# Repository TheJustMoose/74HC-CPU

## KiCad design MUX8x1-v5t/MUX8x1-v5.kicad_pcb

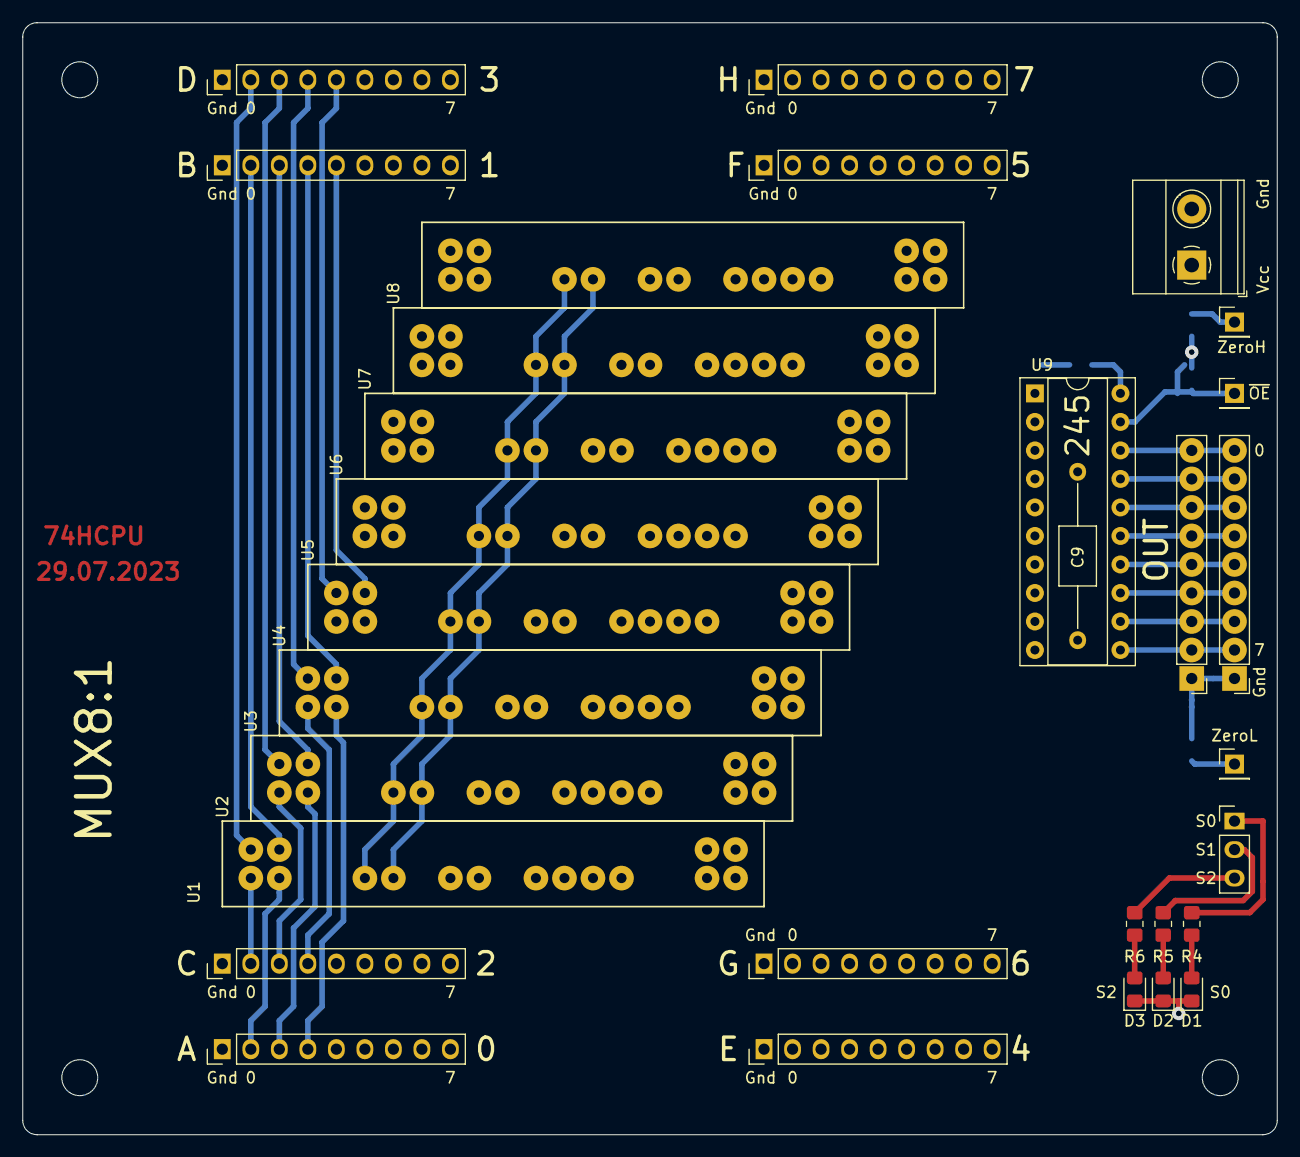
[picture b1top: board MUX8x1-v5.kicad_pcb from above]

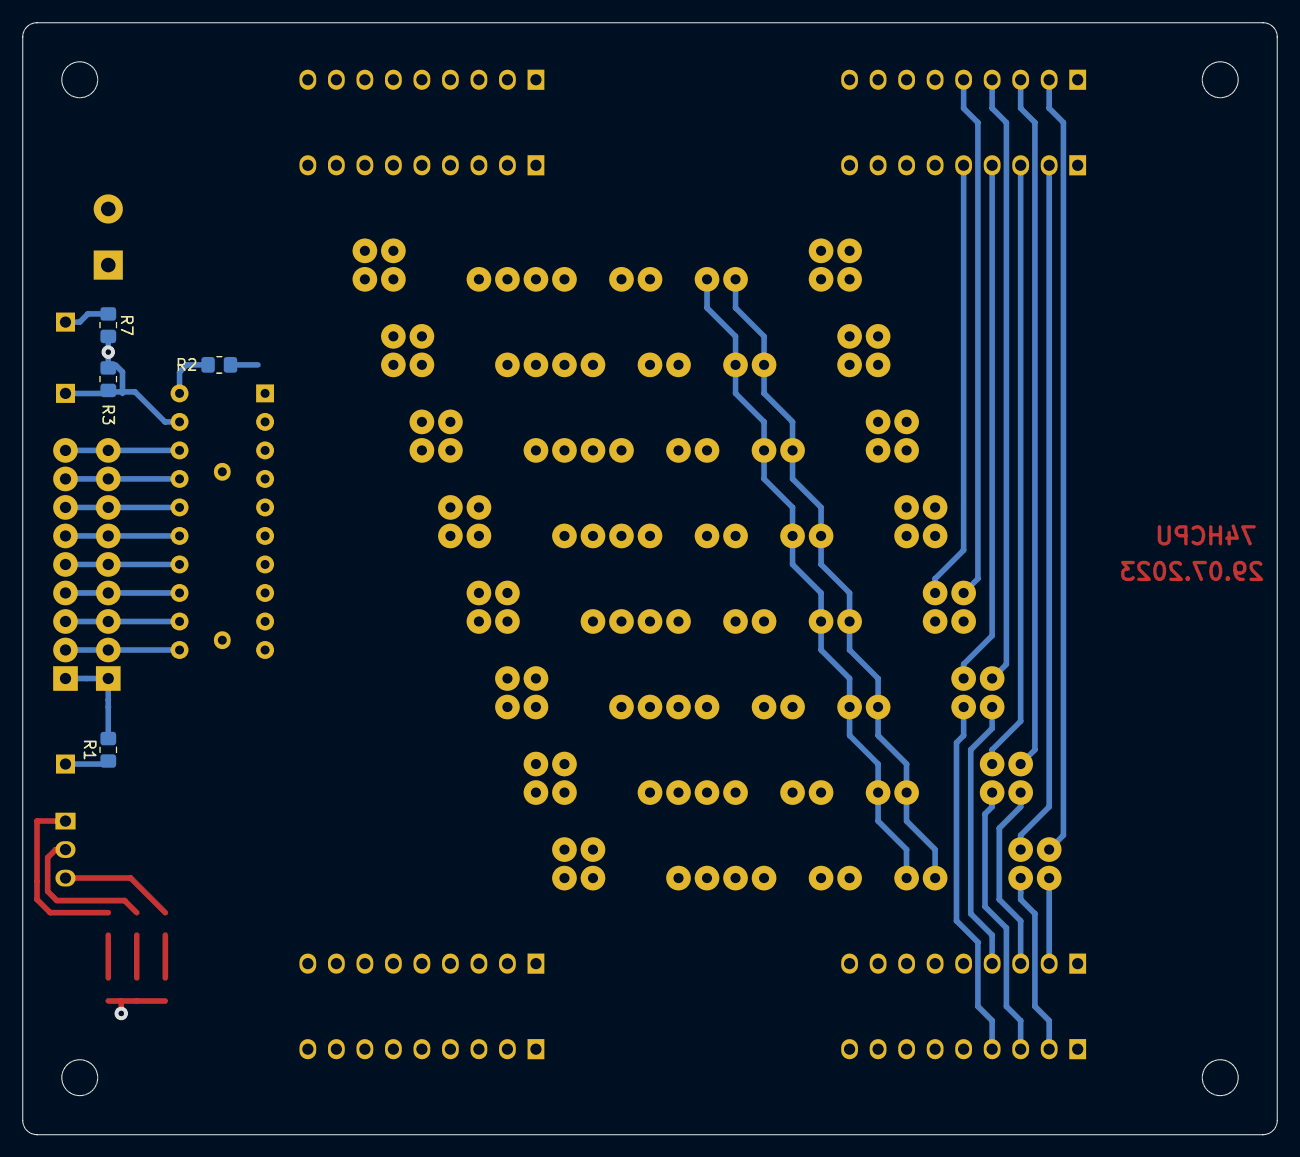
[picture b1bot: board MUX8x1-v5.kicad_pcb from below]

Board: 2 copper layers, 111.8 x 99.1 mm, 39 parts (4 on the bottom side), 92 nets.

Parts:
C9: 0.1uF; C_Axial_L5.1mm_D3.1mm_P15.00mm_Horizontal
D1, D2, D3: LED; LED_0805_2012Metric_Pad1.15x1.40mm_HandSolder
H1, H2, H3, H4: MountingHole; MountingHole_3.2mm_M3
J1, J2, J3, J5, J6, J11, J12, J15, J16, J21: Conn_01x09_Male; PinHeader_1x09_P2.54mm_Vertical
J7, J13, J20: Conn_01x01_Male; PinHeader_1x01_P2.54mm_Vertical
J9: Screw_Terminal_01x02; TerminalBlock_Phoenix_MKDS-1,5-2_1x02_P5.00mm_Horizontal
J10: Conn_01x03_Male; PinHeader_1x03_P2.54mm_Vertical
R1, R2, R3, R7: 10k; R_0805_2012Metric_Pad1.20x1.40mm_HandSolder
R4, R5, R6: 1k; R_0805_2012Metric_Pad1.20x1.40mm_HandSolder
U1, U2, U3, U4, U5, U6, U7, U8: 74LS151; MUX8-1
U9: 74HC245; DIP-20_W7.62mm_Socket

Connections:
/A0: J1.2, U1.4
/A1: J1.3, U2.4
/A2: J1.4, U3.4
/A3: J1.5, U4.4
/A4: J1.6, U5.4
/A5: J1.7, U6.4
/A6: J1.8, U7.4
/A7: J1.9, U8.4
/B0: J5.2, U1.3
/B1: J5.3, U2.3
/B2: J5.4, U3.3
/B3: J5.5, U4.3
/B4: J5.6, U5.3
/B5: J5.7, U6.3
/B6: J5.8, U7.3
/B7: J5.9, U8.3
/BUS0: J3.2, J21.2, U9.11
/BUS1: J3.3, J21.3, U9.12
/BUS2: J3.4, J21.4, U9.13
/BUS3: J3.5, J21.5, U9.14
/BUS4: J3.6, J21.6, U9.15
/BUS5: J3.7, J21.7, U9.16
/BUS6: J3.8, J21.8, U9.17
/BUS7: J3.9, J21.9, U9.18
/C0: J11.2, U1.2
/C1: J11.3, U2.2
/C2: J11.4, U3.2
/C3: J11.5, U4.2
/C4: J11.6, U5.2
/C5: J11.7, U6.2
/C6: J11.8, U7.2
/C7: J11.9, U8.2
/D0: J15.2, U1.1
/D1: J15.3, U2.1
/D2: J15.4, U3.1
/D3: J15.5, U4.1
/D4: J15.6, U5.1
/D5: J15.7, U6.1
/D6: J15.8, U7.1
/D7: J15.9, U8.1
/E0: J2.2, U1.15
/E1: J2.3, U2.15
/E2: J2.4, U3.15
/E3: J2.5, U4.15
/E4: J2.6, U5.15
/E5: J2.7, U6.15
/E6: J2.8, U7.15
/E7: J2.9, U8.15
/F0: J6.2, U1.14
/F1: J6.3, U2.14
/F2: J6.4, U3.14
/F3: J6.5, U4.14
/F4: J6.6, U5.14
/F5: J6.7, U6.14
/F6: J6.8, U7.14
/F7: J6.9, U8.14
/G0: J12.2, U1.13
/G1: J12.3, U2.13
/G2: J12.4, U3.13
/G3: J12.5, U4.13
/G4: J12.6, U5.13
/G5: J12.7, U6.13
/G6: J12.8, U7.13
/G7: J12.9, U8.13
/H0: J16.2, U1.12
/H1: J16.3, U2.12
/H2: J16.4, U3.12
/H3: J16.5, U4.12
/H4: J16.6, U5.12
/H5: J16.7, U6.12
/H6: J16.8, U7.12
/H7: J16.9, U8.12
/O0: U1.5, U9.9
/O1: U2.5, U9.8
/O2: U3.5, U9.7
/O3: U4.5, U9.6
/O4: U5.5, U9.5
/O5: U6.5, U9.4
/O6: U7.5, U9.3
/O7: U8.5, U9.2
/S0: J10.1, R4.2, U1.11, U2.11, U3.11, U4.11, U5.11, U6.11, U7.11, U8.11
/S1: J10.2, R5.2, U1.10, U2.10, U3.10, U4.10, U5.10, U6.10, U7.10, U8.10
/S2: J10.3, R6.2, U1.9, U2.9, U3.9, U4.9, U5.9, U6.9, U7.9, U8.9
/~EH: J20.1, R1.1, U5.7, U6.7, U7.7, U8.7
/~EL: J13.1, R7.1, U1.7, U2.7, U3.7, U4.7
/~OE: J7.1, R3.1, U9.19
GND: C9.2, D1.1, D2.1, D3.1, J1.1, J2.1, J3.1, J5.1, J6.1, J9.2, J11.1, J12.1, J15.1, J16.1, J21.1, R1.2, R3.2, R7.2, U1.8, U2.8, U3.8, U4.8, U5.8, U6.8, U7.8, U8.8, U9.10
unnamed: D1.2, R4.1
unnamed: D2.2, R5.1
unnamed: D3.2, R6.1
unnamed: R2.1, U9.1
VCC: C9.1, J9.1, R2.2, U1.16, U2.16, U3.16, U4.16, U5.16, U6.16, U7.16, U8.16, U9.20

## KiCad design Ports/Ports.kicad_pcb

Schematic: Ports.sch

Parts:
C1, C2, C3: 0.1uF; C_Axial_L3.8mm_D2.6mm_P22.86mm_Horizontal
C4: 0.1uF; C_Rect_L7.0mm_W2.0mm_P5.00mm
D1, D2, D3, D4, D5, D6, D7, D8, D9, D10: LED; LED_Rectangular_W5.0mm_H2.0mm
D11, D12, D13, D14, D15, D16, D17, D18, D19, D20, D21, D22, D23, D24, D25, D26: 6x6-tact-btn; SW_PUSH_6mm_H4.3mm
D27, D28: 1N4148; D_DO-35_SOD27_P10.16mm_Horizontal
DS1: WC1602A; WH1602-2-holes
H1, H2, H3, H4, H5, H6, H7, H8: MountingHole; MountingHole_3.2mm_M3
J1, J2, J3, J6: Conn_01x09_Male; PinHeader_1x09_P2.54mm_Vertical
J4: Screw_Terminal_01x02; TerminalBlock_Phoenix_PT-1,5-2-5.0-H_1x02_P5.00mm_Horizontal
J5: Conn_01x04_Male; PinHeader_1x04_P2.54mm_Vertical
J7, J9: Conn_01x02_Male; PinHeader_1x02_P2.54mm_Vertical
J8: Conn_01x08_Male; PinHeader_1x08_P2.54mm_Vertical
JP1: Jumper; SolderJumper-2_P1.3mm_Open_RoundedPad1.0x1.5mm
Q1: IRLML2060; SOT-23
Q2: IRLML5203; SOT-23
R1: 20; R_Axial_DIN0207_L6.3mm_D2.5mm_P15.24mm_Horizontal
R2, R3, R14, R15, R16, R17, R18, R19, R20, R21, R22: 10k; R_0805_2012Metric_Pad1.20x1.40mm_HandSolder
R4, R5, R6, R7, R8, R9, R10, R11, R12, R13: 1k; R_0805_2012Metric_Pad1.20x1.40mm_HandSolder
RV1: R_POT; pot-5x5
U1, U2, U3: 74LS574; DIP-20_W7.62mm

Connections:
/BUS0: J6.2, U3.12 (Q7)
/BUS1: J6.3, U3.13 (Q6)
/BUS2: J6.4, U3.14 (Q5)
/BUS3: J6.5, U3.15 (Q4)
/BUS4: J6.6, U3.16 (Q3)
/BUS5: J6.7, U3.17 (Q2)
/BUS6: J6.8, U3.18 (Q1)
/BUS7: J6.9, U3.19 (Q0)
/D0: DS1.7 (D0), J1.2, R4.2, U1.2 (D0), U2.2 (D0)
/D1: DS1.8 (D1), J1.3, R5.2, U1.3 (D1), U2.3 (D1)
/D2: DS1.9 (D2), J1.4, R6.2, U1.4 (D2), U2.4 (D2)
/D3: DS1.10 (D3), J1.5, R7.2, U1.5 (D3), U2.5 (D3)
/D4: DS1.11 (D4), J1.6, R8.2, U1.6 (D4), U2.6 (D4)
/D5: DS1.12 (D5), J1.7, R9.2, U1.7 (D5), U2.7 (D5)
/D6: DS1.13 (D6), J1.8, R11.2, U1.8 (D6), U2.8 (D6)
/D7: DS1.14 (D7), J1.9, R13.2, U1.9 (D7), U2.9 (D7)
/IN0.0: D25.1, D26.1, J8.8, R21.1, U3.9 (D7)
/IN0.1: D23.1, D24.1, J8.7, R20.1, U3.8 (D6)
/IN0.2: D21.1, D22.1, J8.6, R19.1, U3.7 (D5)
/IN0.3: D19.1, D20.1, J8.5, R18.1, U3.6 (D4)
/IN0.4: D17.1, D18.1, J8.4, R17.1, U3.5 (D3)
/IN0.5: D15.1, D16.1, J8.3, R16.1, U3.4 (D2)
/IN0.6: D13.1, D14.1, J8.2, R15.1, U3.3 (D1)
/IN0.7: D11.1, D12.1, J8.1, R14.1, U3.2 (D0)
/IN0.C: J7.1, U3.11 (Cp)
/IN0.OE: J7.2, U3.1 (OE)
/OUT0: J5.4, R2.1, U1.11 (Cp)
/OUT1: J5.2, R3.1, U2.11 (Cp)
/OUT2: DS1.6 (E), J5.1, R10.2
/P0.0: DS1.4 (RS), J2.2, R12.2, U1.19 (Q0)
/P0.1: J2.3, U1.18 (Q1)
/P0.2: J2.4, U1.17 (Q2)
/P0.3: J2.5, U1.16 (Q3)
/P0.4: J2.6, U1.15 (Q4)
/P0.5: D27.1 (K), J2.7, U1.14 (Q5)
/P0.6: D28.1 (K), J2.8, U1.13 (Q6)
/P0.7: J2.9, Q1.1 (G), R22.1, U1.12 (Q7)
/P1.0: J3.2, U2.19 (Q0)
/P1.1: J3.3, U2.18 (Q1)
/P1.2: J3.4, U2.17 (Q2)
/P1.3: J3.5, U2.16 (Q3)
/P1.4: J3.6, U2.15 (Q4)
/P1.5: J3.7, U2.14 (Q5)
/P1.6: J3.8, U2.13 (Q6)
/P1.7: J3.9, U2.12 (Q7)
GND: C1.2, C2.2, C3.2, C4.2, DS1.1 (VSS), DS1.5 (R/W), J1.1, J2.1, J3.1, J4.1, J5.3, J6.1, J9.1, J9.2, JP1.2, Q1.2 (S), Q2.1, R2.2, R3.2, R22.2, RV1.1, U1.1 (OE), U1.10 (GND), U2.1 (OE), U2.10 (GND), U3.10 (GND)
unnamed: D1.1 (K), D2.1 (K), D3.1 (K), D4.1 (K), D5.1 (K), D6.1 (K), D7.1 (K), D8.1 (K), D9.1 (K), D10.1 (K), JP1.1
unnamed: D1.2 (A), R4.1
unnamed: D2.2 (A), R5.1
unnamed: D3.2 (A), R6.1
unnamed: D4.2 (A), R7.1
unnamed: D5.2 (A), R8.1
unnamed: D6.2 (A), R9.1
unnamed: D7.2 (A), R10.1
unnamed: D8.2 (A), R11.1
unnamed: D9.2 (A), R12.1
unnamed: D10.2 (A), R13.1
unnamed: D11.2, D13.2, D15.2, D17.2, D19.2, D21.2, D23.2, D25.2, D27.2 (A)
unnamed: D12.2, D14.2, D16.2, D18.2, D20.2, D22.2, D24.2, D26.2, D28.2 (A)
unnamed: DS1.3 (VO), RV1.2
unnamed: DS1.15 (LED(+)), R1.2
unnamed: DS1.16 (LED(-)), Q1.3 (D)
unnamed: J4.2, Q2.3
VCC: C1.1, C2.1, C3.1, C4.1, DS1.2 (VDD), Q2.2, R1.1, R14.2, R15.2, R16.2, R17.2, R18.2, R19.2, R20.2, R21.2, RV1.3, U1.20 (VCC), U2.20 (VCC), U3.20 (VCC)

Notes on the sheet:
OUT

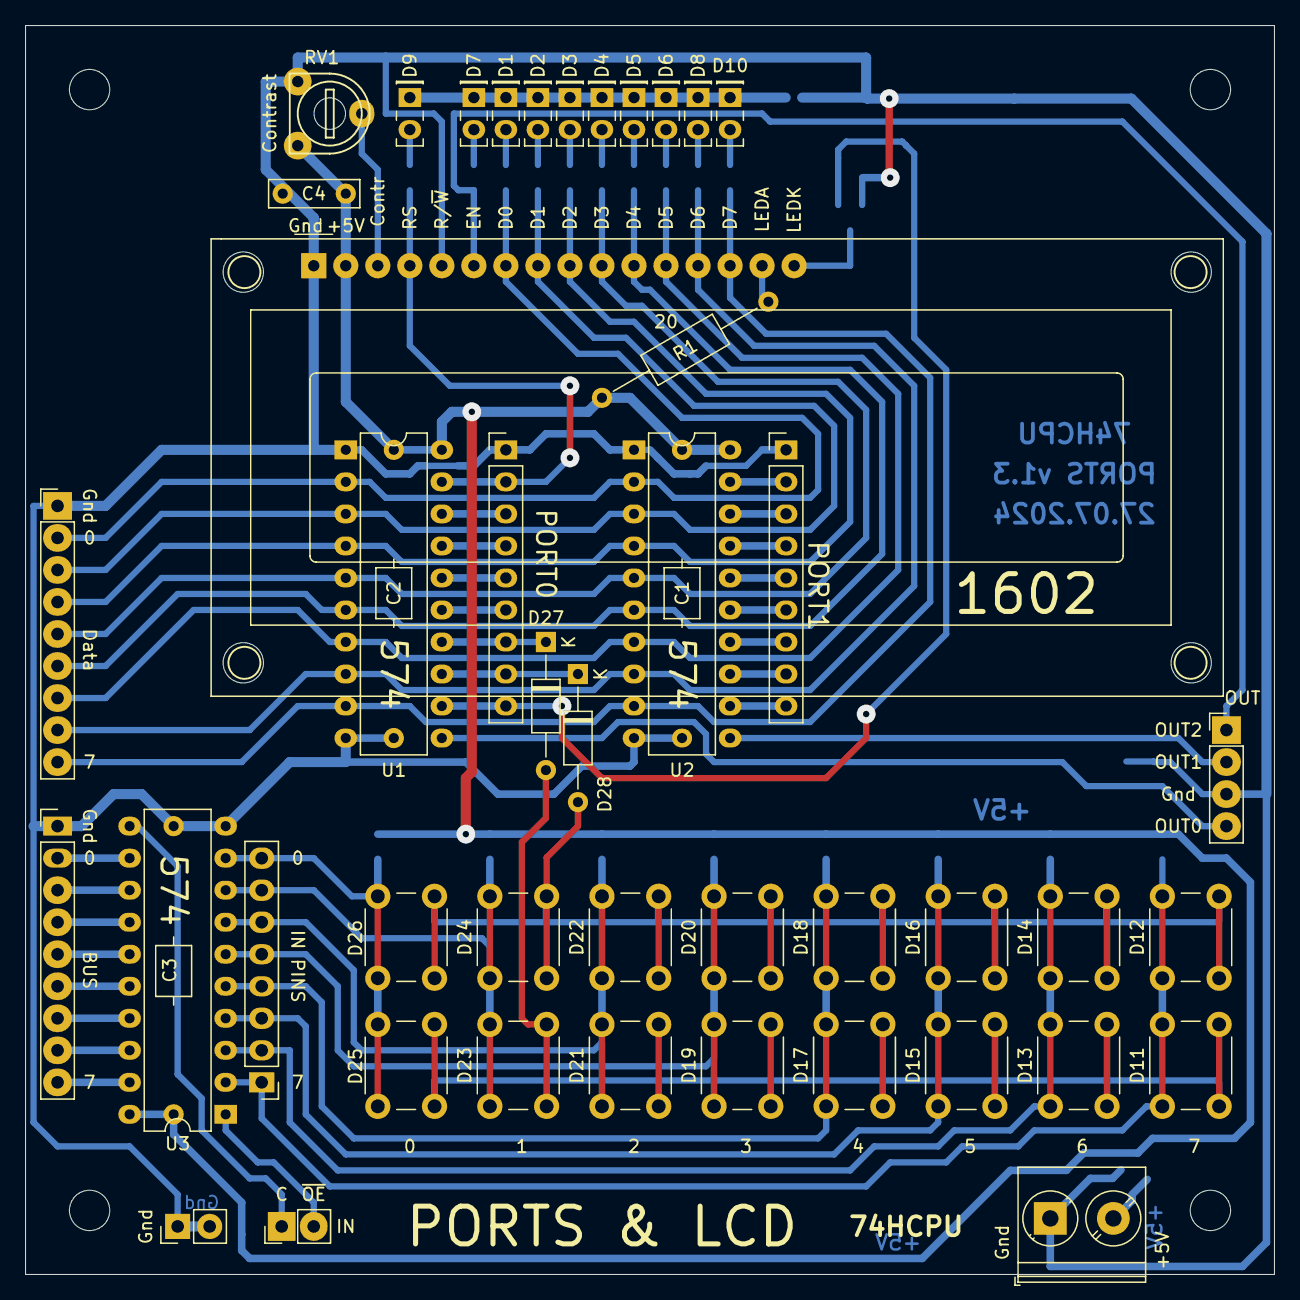
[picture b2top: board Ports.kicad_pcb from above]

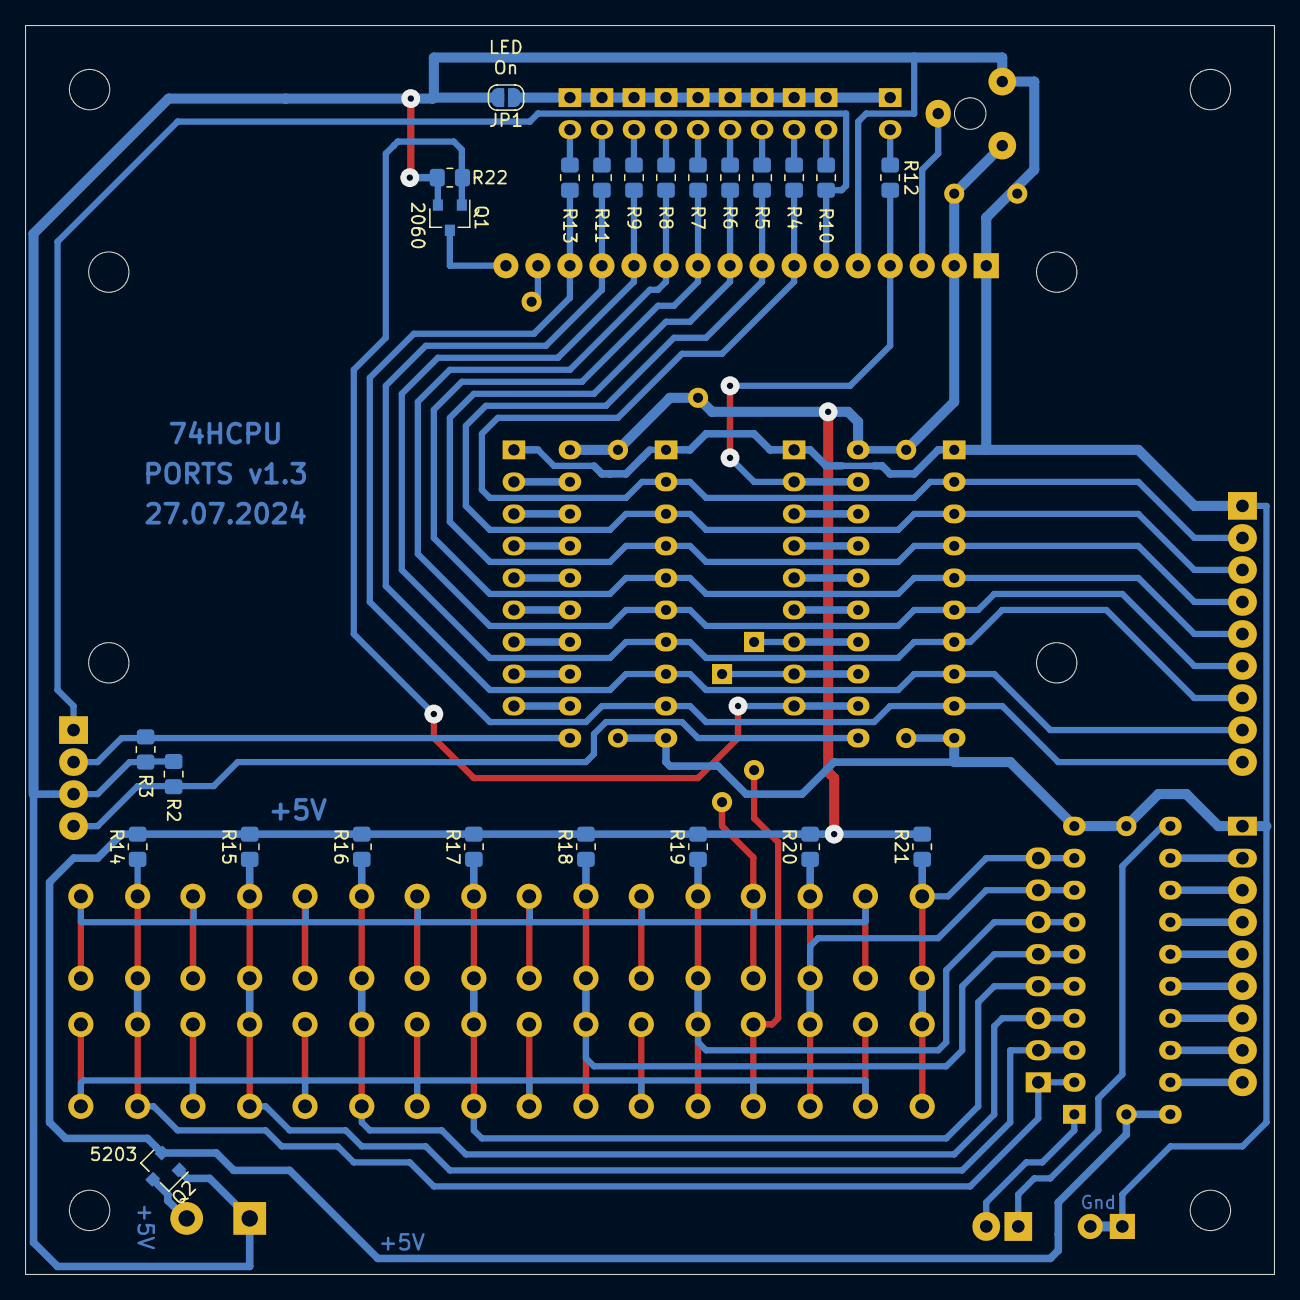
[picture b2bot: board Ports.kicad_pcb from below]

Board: 2 copper layers, 99.1 x 99.1 mm, 79 parts (24 on the bottom side), 64 nets.

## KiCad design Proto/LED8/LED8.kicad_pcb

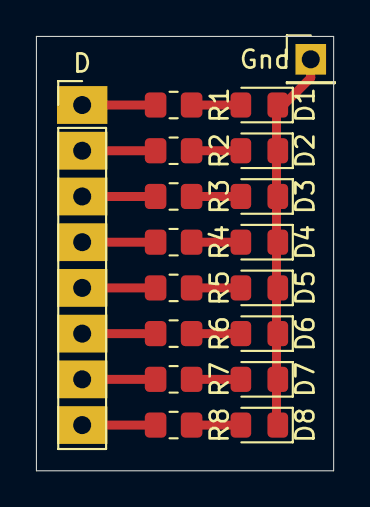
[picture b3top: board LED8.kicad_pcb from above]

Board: 2 copper layers, 16.5 x 24.1 mm, 18 parts (0 on the bottom side), 17 nets.

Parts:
D: Conn_01x08_Male; PinHeader_1x08_P2.54mm_Vertical
D1, D2, D3, D4, D5, D6, D7, D8: LED; LED_0805_2012Metric_Pad1.15x1.40mm_HandSolder
Gnd: Conn_01x01_Male; PinHeader_1x01_P2.54mm_Vertical
R1, R2, R3, R4, R5, R6, R7, R8: 1k; R_0805_2012Metric_Pad1.20x1.40mm_HandSolder

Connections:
unnamed: D1.1, D2.1, D3.1, D4.1, D5.1, D6.1, D7.1, D8.1, Gnd.1
unnamed: D1.2, R1.1
unnamed: D2.2, R2.1
unnamed: D3.2, R3.1
unnamed: D4.2, R4.1
unnamed: D5.2, R5.1
unnamed: D6.2, R6.1
unnamed: D7.2, R7.1
unnamed: D8.2, R8.1
unnamed: D.1, R1.2
unnamed: D.2, R2.2
unnamed: D.3, R3.2
unnamed: D.4, R4.2
unnamed: D.5, R5.2
unnamed: D.6, R6.2
unnamed: D.7, R7.2
unnamed: D.8, R8.2
